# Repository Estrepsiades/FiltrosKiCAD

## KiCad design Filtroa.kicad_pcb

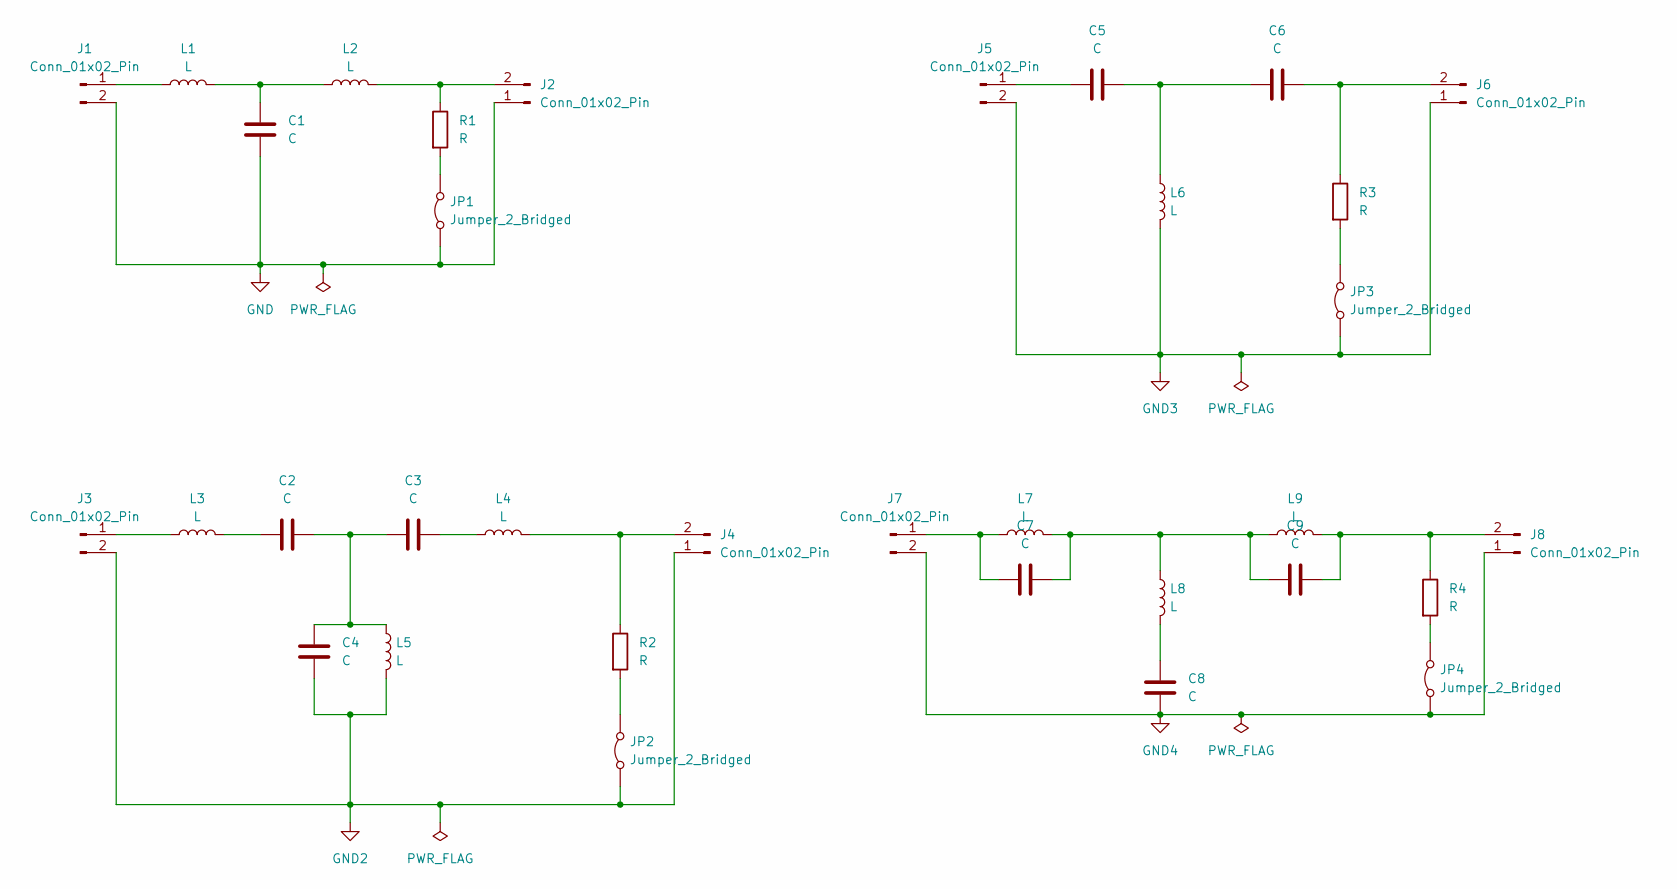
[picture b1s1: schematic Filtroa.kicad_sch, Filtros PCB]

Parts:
C1, C2, C3, C4, C5, C6, C7, C8, C9: C; C_0201_0603Metric
J1, J2, J3, J4, J5, J6, J7, J8: Conn_01x02_Pin; PinHeader_1x02_P1.00mm_Horizontal
JP1, JP2, JP3, JP4: Jumper_2_Bridged; TestPoint_2Pads_Pitch2.54mm_Drill0.8mm
L1, L2, L3, L4, L5, L6, L7, L8, L9: L; L_0201_0603Metric
R1, R2, R3, R4: R; R_0201_0603Metric

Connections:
GND: C1.2, J1.2, J2.1, JP1.1 (A)
GND2: C4.2, J3.2, J4.1, JP2.1 (A), L5.2
GND3: J5.2, J6.1, JP3.1 (A), L6.2
GND4: C8.2, J7.2, J8.1, JP4.1 (A)
unnamed: C1.1, L1.2, L2.1
unnamed: C2.1, L3.2
unnamed: C2.2, C3.1, C4.1, L5.1
unnamed: C3.2, L4.1
unnamed: C5.2, C6.1, L6.1
unnamed: C7.2, C9.1, L7.2, L8.1, L9.1
unnamed: C8.1, L8.2
unnamed: J1.1, L1.1
unnamed: J2.2, L2.2, R1.1
unnamed: J3.1, L3.1
unnamed: J4.2, L4.2, R2.1
unnamed: C5.1, J5.1
unnamed: C6.2, J6.2, R3.1
unnamed: C7.1, J7.1, L7.1
unnamed: C9.2, J8.2, L9.2, R4.1
unnamed: JP1.2 (B), R1.2
unnamed: JP2.2 (B), R2.2
unnamed: JP3.2 (B), R3.2
unnamed: JP4.2 (B), R4.2

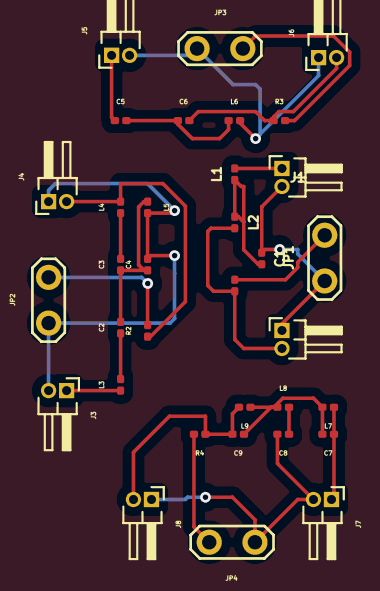
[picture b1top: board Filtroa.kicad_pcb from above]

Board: 2 copper layers, 34 parts (0 on the bottom side), 23 nets.
